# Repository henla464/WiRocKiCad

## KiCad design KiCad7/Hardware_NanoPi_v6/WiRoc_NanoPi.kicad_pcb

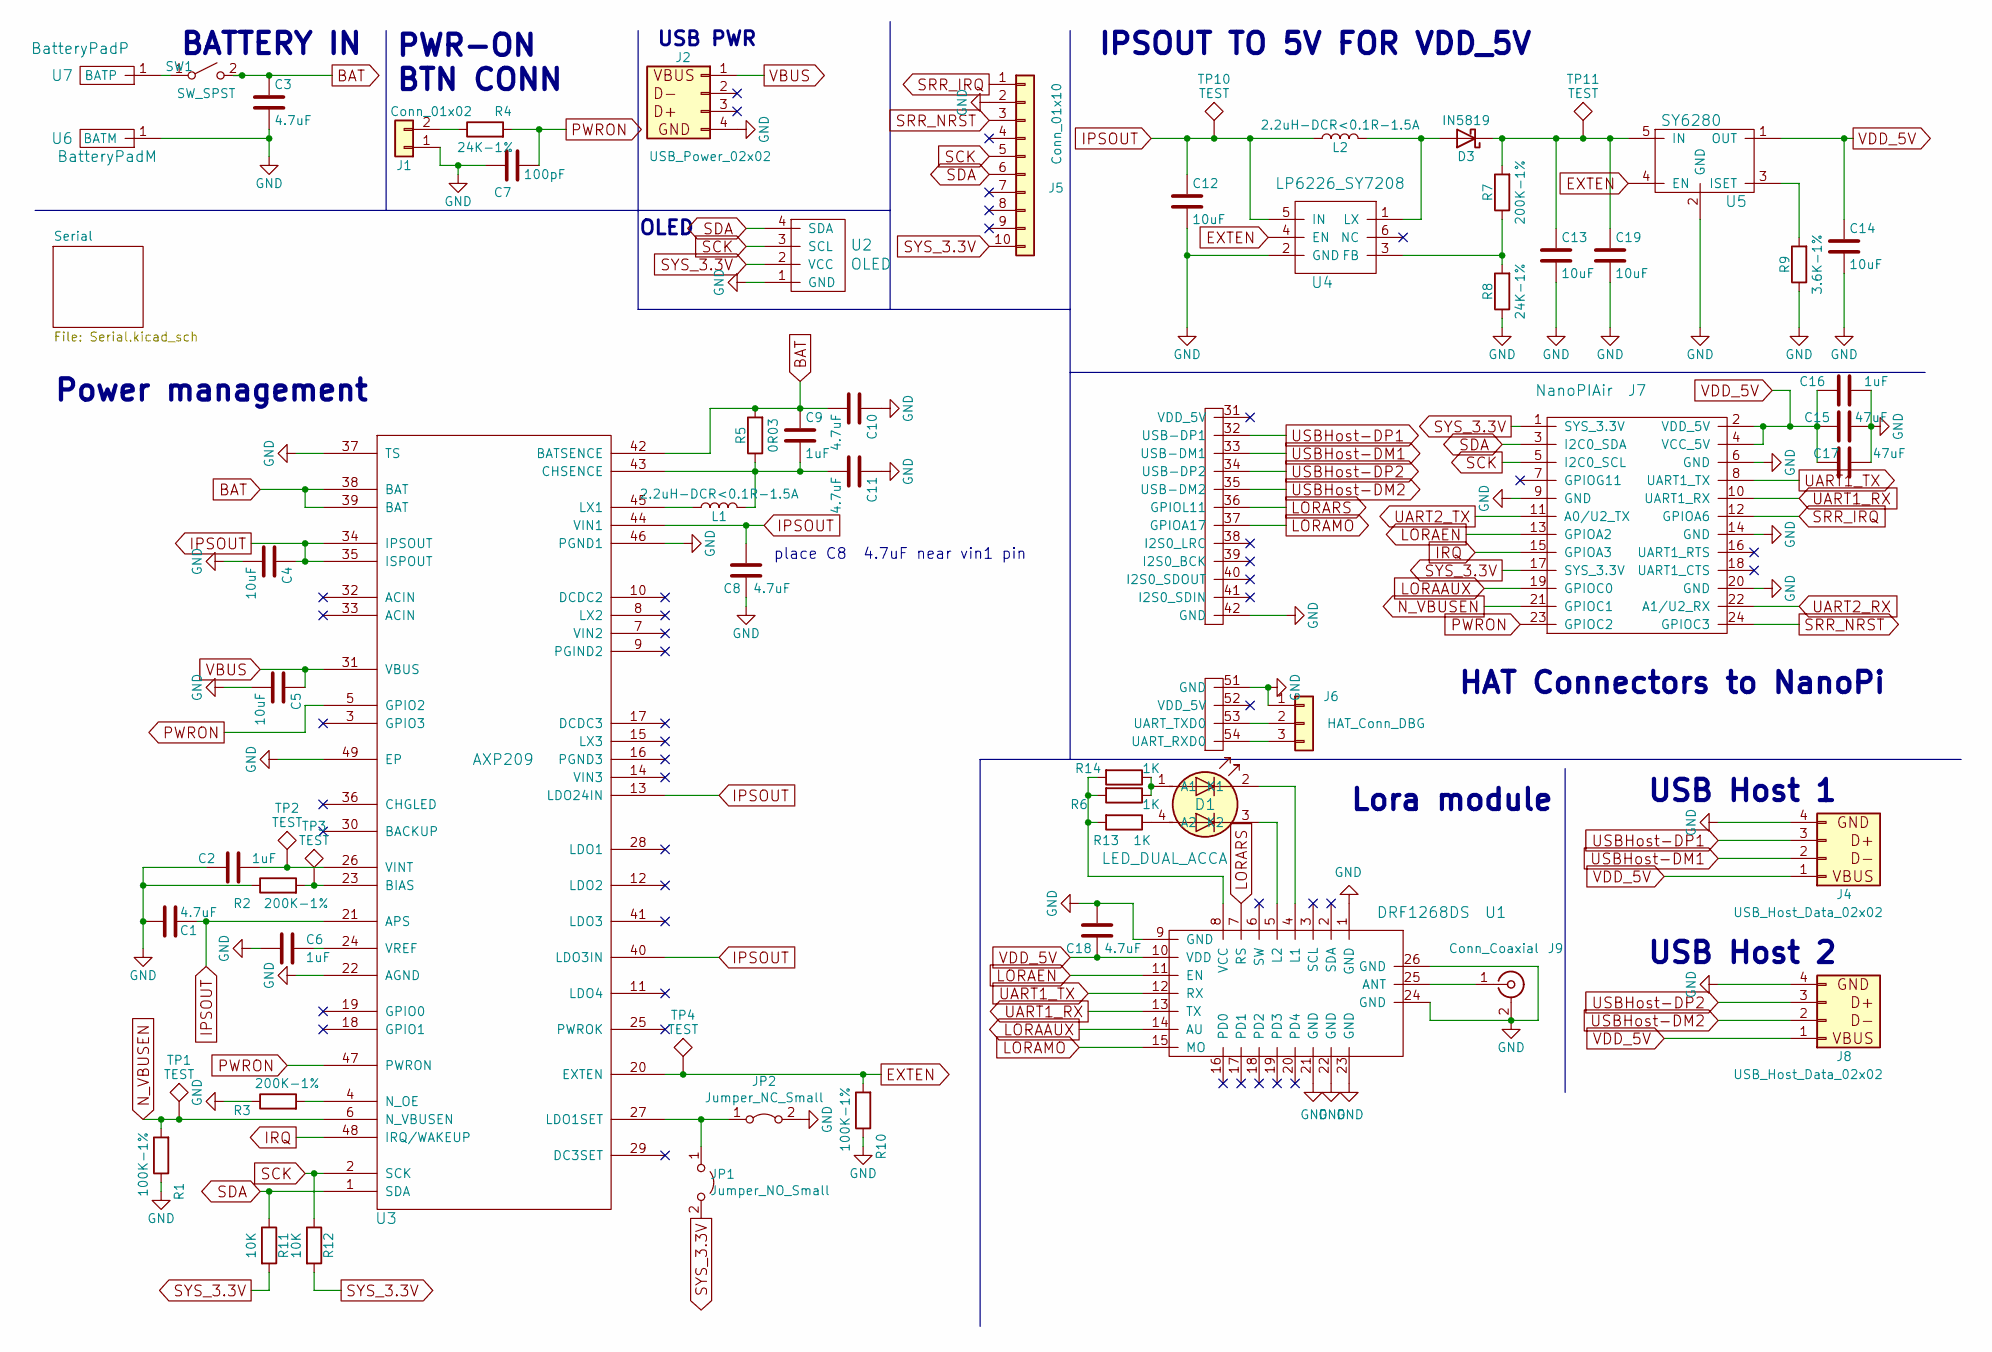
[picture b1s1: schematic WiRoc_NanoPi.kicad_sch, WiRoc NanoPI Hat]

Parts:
C1, C3, C8, C10, C11, C18: 4.7uF; C_0603_1608Metric; ManufacturerPartNumber CL10A475KO8NNNC; LCSC Part # C19666
C2, C6, C9, C16: 1uF; C_0603_1608Metric; ManufacturerPartNumber CL10A105KB8NNNC; LCSC Part # C15849
C4, C5, C12, C13, C14, C19: 10uF; C_0603_1608Metric; ManufacturerPartNumber CL10A106KP8NNNC; LCSC Part # C19702
C7: 100pF; C_0603_1608Metric; ManufacturerPartNumber CL10C101JB8NNNC; LCSC Part # C14858
C15: 47uF; C_1206_3216Metric; ManufacturerPartNumber CL31A476MPHNNNE; LCSC Part # C96123
C17: 47uF; C_1206_3216Metric; ManufacturerPartNumber CL31A476MPHNNNE; LCSC Part # C93123
D1: LED_DUAL_ACCA; LED_Dual_1.7_1.6; ManufacturerPartNumber HL-PCB-1617S9FH203BC; LCSC Part # C513363
D3: IN5819; D_SOD-123; ManufacturerPartNumber B5819W SL; LCSC Part # C8598
J1: Conn_01x02; Pin_Header_Straight_1x02_Pitch2.54mm; ManufacturerPartNumber 2.54mm 1x40P
J2: USB_Power_02x02; USBConnPads5
J4: USB_Host_Data_02x02; USBConnPads5
J5: Conn_01x10; FPC-Connector_1x10-1MP_P0.5mm_Horizontal; ManufacturerPartNumber X05B20U10T; LCSC Part # C388696
J6: HAT_Conn_DBG; Pin_Header_Straight_1x03_Pitch2.54mm; ManufacturerPartNumber 2.54mm 1x40P
J7: NanoPIAir; NanoPiNeoAirAllPins; ManufacturerPartNumber 2.54mm 2x40P
J8: USB_Host_Data_02x02; USBConnPads6
J9: Conn_Coaxial; SMA_Amphenol_901-143_Horizontal
JP1: Jumper_NO_Small; SolderJumper-2_P1.3mm_Open_Pad1.0x1.5mm-Modified
JP2: Jumper_NC_Small; SolderJumper-2_P1.3mm_Bridged2Bar_Pad1.0x1.5mm-Modified
L1, L2: 2.2uH-DCR<0.1R-1.5A; Inductor_SLW4018; ManufacturerPartNumber SLW4018S2R2MST; LCSC Part # C206341
R1, R10: 100K-1%; R_0603_1608Metric; ManufacturerPartNumber 0603WAF1003T5E; LCSC Part # C25803
R2, R3, R7: 200K-1%; R_0603_1608Metric; ManufacturerPartNumber 0603WAF2003T5E; LCSC Part # C25811
R4, R8: 24K-1%; R_0603_1608Metric; ManufacturerPartNumber 0603WAF2402T5E; LCSC Part # C23352
R5: 0R03; R_0805_2012Metric; ManufacturerPartNumber 0805W4F300MT5E; LCSC Part # C247605
R6, R13, R14: 1K; R_0603_1608Metric; ManufacturerPartNumber 0603WAJ0102T5E; LCSC Part # C25585
R9: 3.6K-1%; R_0603_1608Metric; ManufacturerPartNumber 0603WAF3601T5E; LCSC Part # C22980
R11, R12: 10K; R_0603_1608Metric; ManufacturerPartNumber 0603WAF1002T5E; LCSC Part # C25804
SW1: SW_SPST; Pin_Header_Straight_1x02_Pitch2.54mm; ManufacturerPartNumber 2.54mm 1x40P
TP1, TP2, TP3, TP4, TP10, TP11: TEST; TestPoint_Pad_D1.0mm
U1: DRF1268DS
U2: OLED; CONN_OLED_TWI-Socket_Strip_Straight_1x04_Pitch2.54mm; ManufacturerPartNumber 2.54mm 1x40P
U3: AXP209; qfn48_6x6mm_Pitch0.4mm; ManufacturerPartNumber AXP209; LCSC Part # C2997895
U4: LP6226_SY7208; SOT-23-6; ManufacturerPartNumber SY7208ABC; LCSC Part # C80514
U5: SY6280; SOT-23-5; ManufacturerPartNumber SY6280AAC; LCSC Part # C55136
U6: BatteryPadM; BatteryPad
U7: BatteryPadP; BatteryPad

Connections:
BAT: C3.1, C9.1, C10.2, R5.2, SW1.2 (B), U3.38 (BAT), U3.39 (BAT), U3.42 (BATSENCE)
EXTEN: R10.2, TP4.1, U3.20 (EXTEN), U4.4 (EN), U5.4 (EN)
GND: C1.2, C2.2, C3.2, C4.2, C5.2, C6.2, C7.1, C8.1, C10.1, C11.1, C12.2, C13.2, C14.2, C15.1, C16.2, C17.1, C18.2, C19.2, J1.1, J2.4, J4.4, J5.2, J6.1, J7.6 (GND), J7.9 (GND), J7.14 (GND), J7.20 (GND), J7.42 (GND), J7.51 (GND), J8.4, J9.2 (Ext), JP2.2 (B), R1.1, R2.1, R3.1, R8.1, R9.1, R10.1, U1.1 (GND), U1.9 (GND), U1.21 (GND), U1.22 (GND), U1.23 (GND), U1.24 (GND), U1.26 (GND), U2.1 (GND), U3.22 (AGND), U3.37 (TS), U3.46 (PGND1), U3.49 (EP), U4.2 (GND), U5.2 (GND), U6.1 (BATM); also elsewhere on the board
IPSOUT: C1.1, C4.1, C8.2, C12.1, L2.1, TP10.1, U3.13 (LDO24IN), U3.21 (APS), U3.34 (IPSOUT), U3.35 (ISPOUT), U3.40 (LDO3IN), U3.44 (VIN1), U4.5 (IN)
IRQ: J7.15 (GPIOA3), U3.48 (IRQ/WAKEUP)
LORAAUX: J7.19 (GPIOC0), U1.14 (AU)
LORAEN: J7.13 (GPIOA2), U1.11 (EN)
LORAMO: J7.37 (GPIOA17), U1.15 (MO)
LORARS: J7.36 (GPIOL11), U1.7 (RS)
N_VBUSEN: J7.21 (GPIOC1), R1.2, TP1.1, U3.6 (N_VBUSEN)
unnamed: D1.1 (A1), R6.1, R14.1
unnamed: D1.4 (A2), R13.1
unnamed: D1.2 (K1), U1.4 (L1)
unnamed: D1.3 (K2), U1.5 (L2)
unnamed: D3.2 (A), L2.2, U4.1 (LX)
unnamed: C13.1, C19.1, D3.1 (K), R7.2, TP11.1, U5.5 (IN)
unnamed: J1.2, R4.1
unnamed: J6.2, J7.53 (UART_TXD0)
unnamed: J6.3, J7.54 (UART_RXD0)
unnamed: J9.1 (In), U1.25 (ANT)
unnamed: JP1.1 (A), JP2.1 (A), U3.27 (LDO1SET)
unnamed: SW1.1 (A), U7.1 (BATP)
unnamed: R6.2, R13.2, R14.2, U1.8 (VCC)
unnamed: R2.2, TP3.1, U3.23 (BIAS)
unnamed: C9.2, C11.2, L1.2, R5.1, U3.43 (CHSENCE)
unnamed: L1.1, U3.45 (LX1)
unnamed: R3.2, U3.4 (N_OE)
unnamed: C2.1, TP2.1, U3.26 (VINT)
unnamed: C6.1, U3.24 (VREF)
unnamed: R7.1, R8.2, U4.3 (FB)
unnamed: R9.2, U5.3 (ISET)
PWRON: C7.2, J7.23 (GPIOC2), R4.2, U3.5 (GPIO2), U3.47 (PWRON)
SCK: J5.5, J7.5 (I2C0_SCL), R12.1, U2.3 (SCL), U3.2 (SCK)
SDA: J5.6, J7.3 (I2C0_SDA), R11.1, U2.4 (SDA), U3.1 (SDA)
SRR_IRQ: J5.1, J7.12 (GPIOA6)
SRR_NRST: J5.3, J7.24 (GPIOC3)
SYS_3.3V: J5.10, J7.1 (SYS_3.3V), J7.17 (SYS_3.3V), JP1.2 (B), R11.2, R12.2, U2.2 (VCC); also elsewhere on the board
UART1_RX: J7.10 (UART1_RX), U1.13 (TX)
UART1_TX: J7.8 (UART1_TX), U1.12 (RX)
UART2_RX: J7.22 (A1/U2_RX); also elsewhere on the board
UART2_TX: J7.11 (A0/U2_TX); also elsewhere on the board
USBHost-DM1: J4.2, J7.33 (USB-DM1)
USBHost-DM2: J7.35 (USB-DM2), J8.2
USBHost-DP1: J4.3, J7.32 (USB-DP1)
USBHost-DP2: J7.34 (USB-DP2), J8.3
VBUS: C5.1, J2.1, U3.31 (VBUS)
VDD_5V: C14.1, C15.2, C16.1, C17.2, C18.1, J4.1, J7.2 (VDD_5V), J7.4 (VCC_5V), J8.1, U1.10 (VDD), U5.1 (OUT)

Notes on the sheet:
place C8 4.7uF near vin1 pin
USB PWR
USB Host 2
Lora module
HAT Connectors to NanoPi
IPSOUT TO 5V FOR VDD_5V
PWR-ON BTN CONN
Power management
OLED
USB Host 1
BATTERY IN

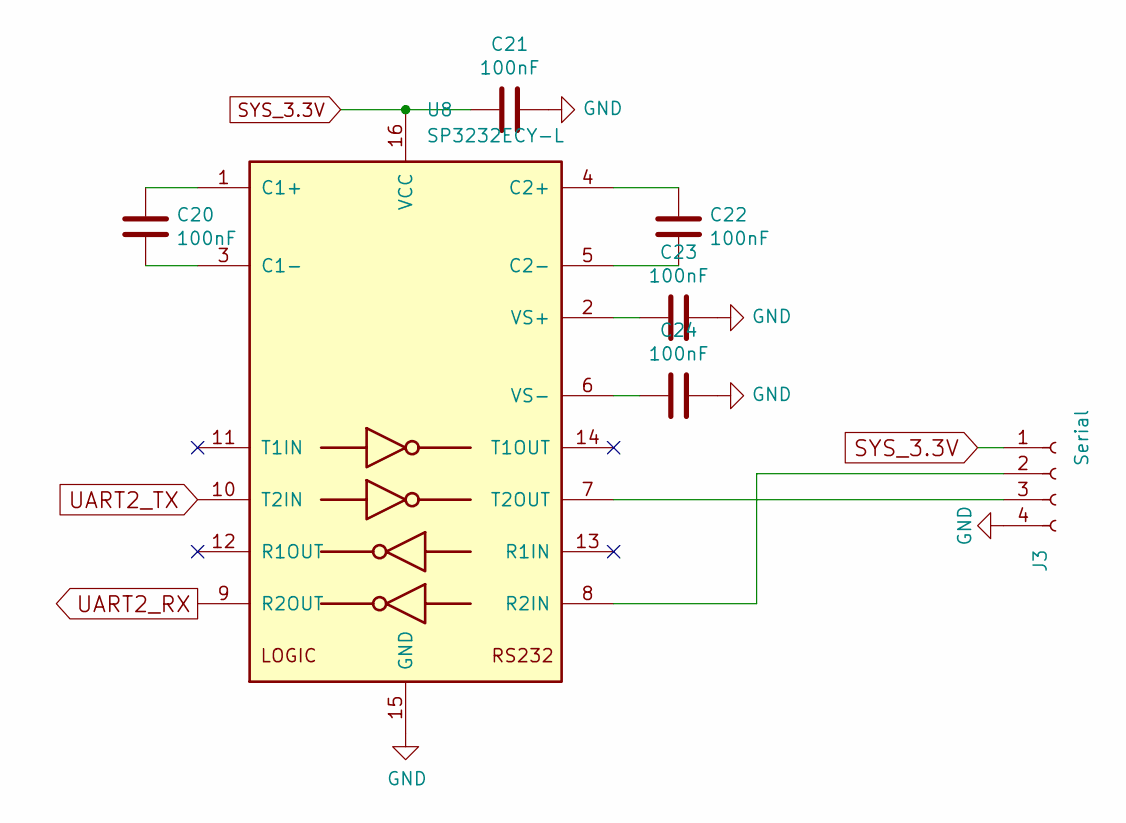
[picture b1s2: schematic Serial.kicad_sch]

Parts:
C20, C21, C22, C23, C24: 100nF; C_0603_1608Metric; ManufacturerPartNumber CC0603KRX7R9BB104; LCSC Part # C14663
J3: Serial; SerialConnPads
U8: SP3232ECY-L; TSSOP-16_4.4x5mm_P0.65mm; ManufacturerPartNumber SP3232ECY-L; LCSC Part # C31142

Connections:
GND: C21.1, C23.1, C24.1, J3.4, U8.15 (GND); also elsewhere on the board
unnamed: J3.2, U8.8 (R2IN)
unnamed: J3.3, U8.7 (T2OUT)
unnamed: C20.1, U8.1 (C1+)
unnamed: C20.2, U8.3 (C1-)
unnamed: C22.1, U8.4 (C2+)
unnamed: C22.2, U8.5 (C2-)
unnamed: C23.2, U8.2 (VS+)
unnamed: C24.2, U8.6 (VS-)
SYS_3.3V: C21.2, J3.1, U8.16 (VCC); also elsewhere on the board
UART2_RX: U8.9 (R2OUT); also elsewhere on the board
UART2_TX: U8.10 (T2IN); also elsewhere on the board

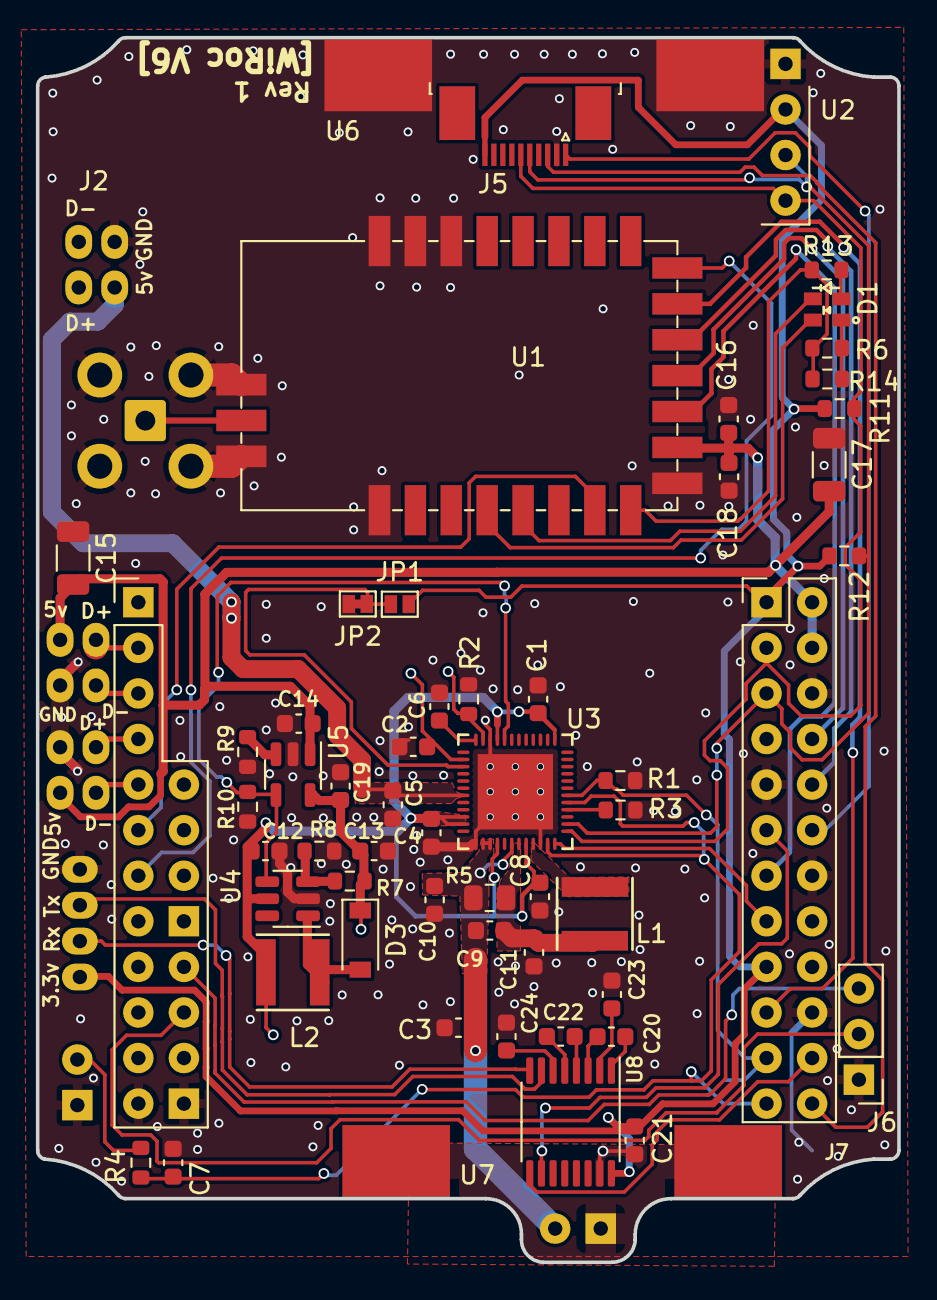
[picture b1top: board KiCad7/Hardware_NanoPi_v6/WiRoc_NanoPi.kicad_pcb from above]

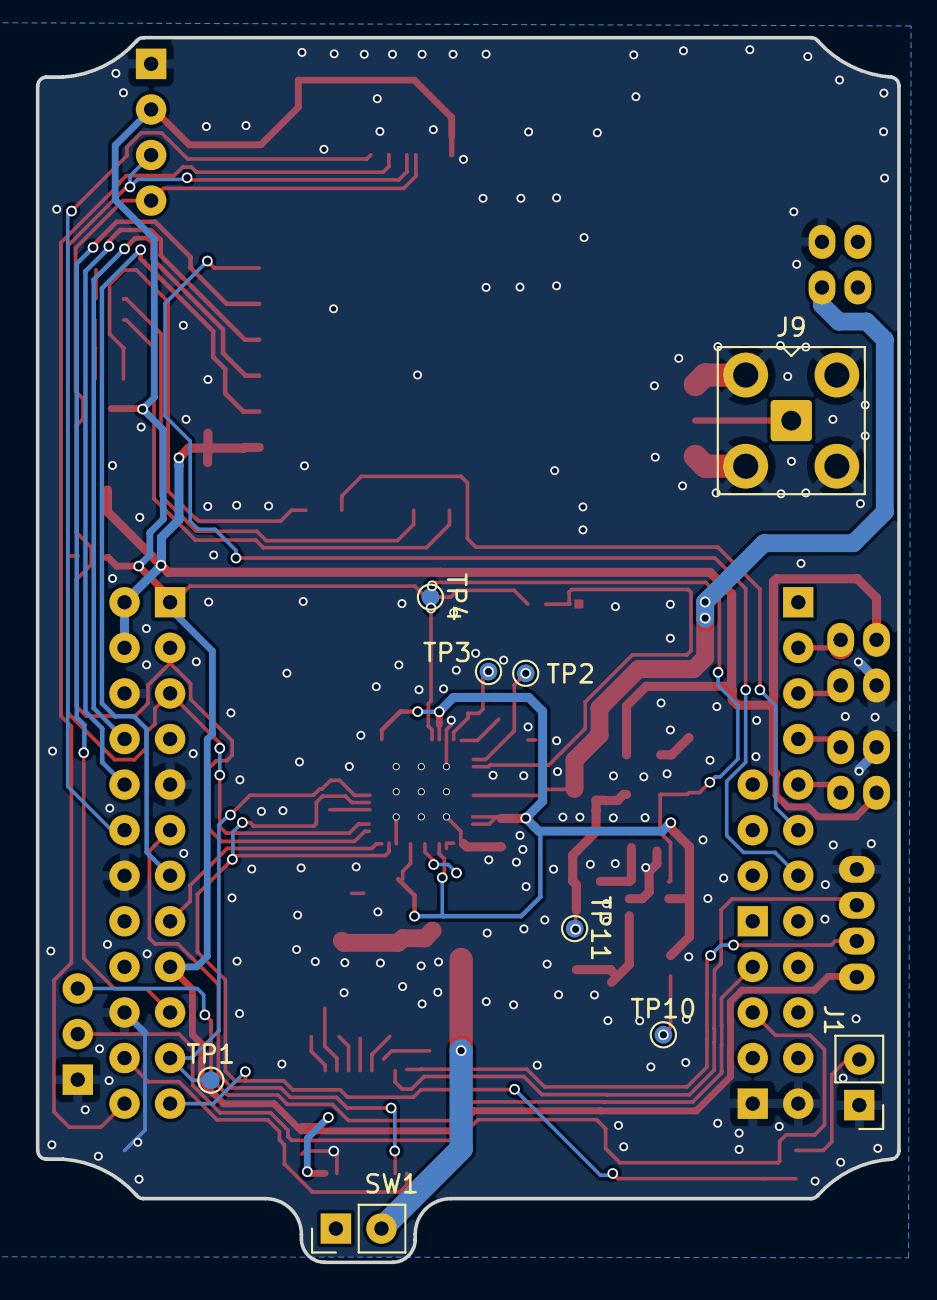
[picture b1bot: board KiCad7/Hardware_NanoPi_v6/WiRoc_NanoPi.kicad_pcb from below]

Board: 4 copper layers, 48.0 x 68.2 mm, 68 parts (9 on the bottom side), 55 nets.

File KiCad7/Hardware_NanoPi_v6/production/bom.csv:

Designator,Footprint,Quantity,Value,LCSC Part #
"C1, C10, C11, C18, C3, C8",0603,6,4.7uF,C19666
"C12, C13, C14, C19, C4, C5",0603,6,10uF,C19702
"C15, C17",1206,2,47uF,C93123
"C16, C2, C6, C9",0603,4,1uF,C15849
"C20, C21, C22, C23, C24",0603,5,100nF,C14663
C7,0603,1,100pF,C14858
D1,LED_Dual_1.7_1.6,1,LED_DUAL_ACCA,C513363
D3,D_SOD-123,1,IN5819,C8598
J5,FPC-Connector_1x10-1MP_P0.5mm_Horizontal,1,Conn_01x10,C388696
"L1, L2",Inductor_SLW4018,2,2.2uH-DCR<0.1R-1.5A,C206341
"R1, R10",0603,2,100K-1%,C25803
"R11, R12",0603,2,10K,C25804
"R13, R14, R6",0603,3,1K,C25585
"R2, R3, R7",0603,3,200K-1%,C25811
"R4, R8",0603,2,24K-1%,C23352
R5,0805,1,0R03,C247605
R9,0603,1,3.6K-1%,C22980
U3,qfn48_6x6mm_Pitch0.4mm,1,AXP209,C2997895
U4,SOT-23-6,1,LP6226_SY7208,C80514
U5,SOT-23-5,1,SY6280,C55136
U8,TSSOP-16_4.4x5mm_P0.65mm,1,SP3232ECY-L,C31142

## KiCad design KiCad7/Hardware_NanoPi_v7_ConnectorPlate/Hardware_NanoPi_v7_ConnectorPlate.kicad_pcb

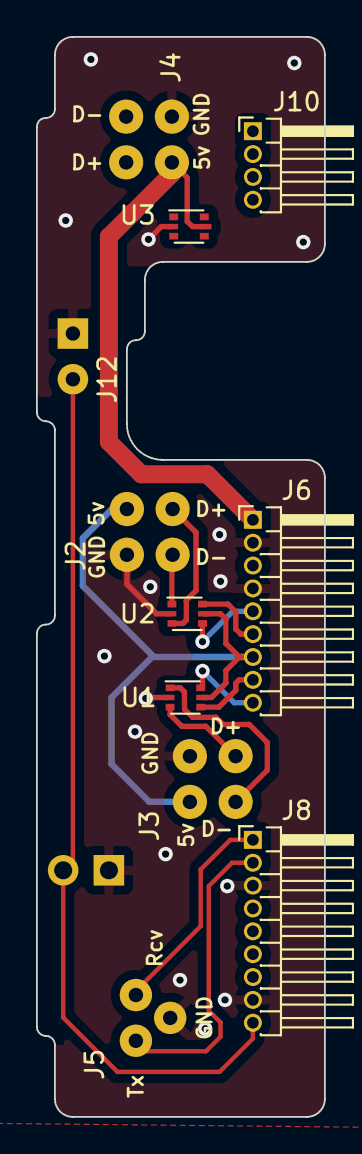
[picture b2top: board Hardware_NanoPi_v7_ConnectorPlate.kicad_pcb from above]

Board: 2 copper layers, 16.0 x 60.0 mm, 12 parts (1 on the bottom side), 14 nets.

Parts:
J2: USB_Host_Data_02x02; USBConnPads7
J3: USB_Host_Data_02x02; USBConnPads8
J4: USB_Power_02x02; USBConnPads7
J5: Conn_01x03; SerialConnPads3Pin
J6, J8: Conn_01x09; PinHeader_1x09_P1.27mm_Horizontal
J10: Conn_01x04; PinHeader_1x04_P1.27mm_Horizontal
J11: Conn_01x02; PinHeader_1x02_P2.54mm_Horizontal
J12: Conn_01x02; PwrBtnPads
U1, U2, U3: USBLC6-2P6; SOT-666

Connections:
GND: J2.4, J3.4, J4.4, J5.3, J6.2, J6.4, J8.3, J8.8, J11.1, J12.1, U1.2 (GND), U2.2 (GND), U3.2 (GND)
unnamed: J2.2, U2.1 (I/O1)
unnamed: J2.3, U2.3 (I/O2)
unnamed: J3.2, U1.1 (I/O1)
unnamed: J3.3, U1.3 (I/O2)
PWRBTN: J8.9, J11.2, J12.2
R2IN: J5.1, J8.2
T2OUT: J5.2, J8.1
USBHost-DM1: J6.6, U2.6 (I/O1)
USBHost-DM2: J6.9, U1.6 (I/O1)
USBHost-DP1: J6.5, U2.4 (I/O2)
USBHost-DP2: J6.8, U1.4 (I/O2)
VBUS: J4.1, J6.1, U3.5 (VBUS)
VDD_5V: J2.1, J3.1, J6.7, U1.5 (VBUS), U2.5 (VBUS)

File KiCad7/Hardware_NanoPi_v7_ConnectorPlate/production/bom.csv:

Designator,Footprint,Quantity,Value,LCSC Part #
J10,PinHeader_1x04_P1.27mm_Horizontal,1,Conn_01x04,
J11,PinHeader_1x02_P2.54mm_Horizontal,1,Conn_01x02,
J12,PwrBtnPads,1,Conn_01x02,
J5,SerialConnPads3Pin,1,Conn_01x03,
"J6, J8",PinHeader_1x09_P1.27mm_Horizontal,2,Conn_01x09,
"U1, U2, U3",SOT-666,3,USBLC6-2P6,

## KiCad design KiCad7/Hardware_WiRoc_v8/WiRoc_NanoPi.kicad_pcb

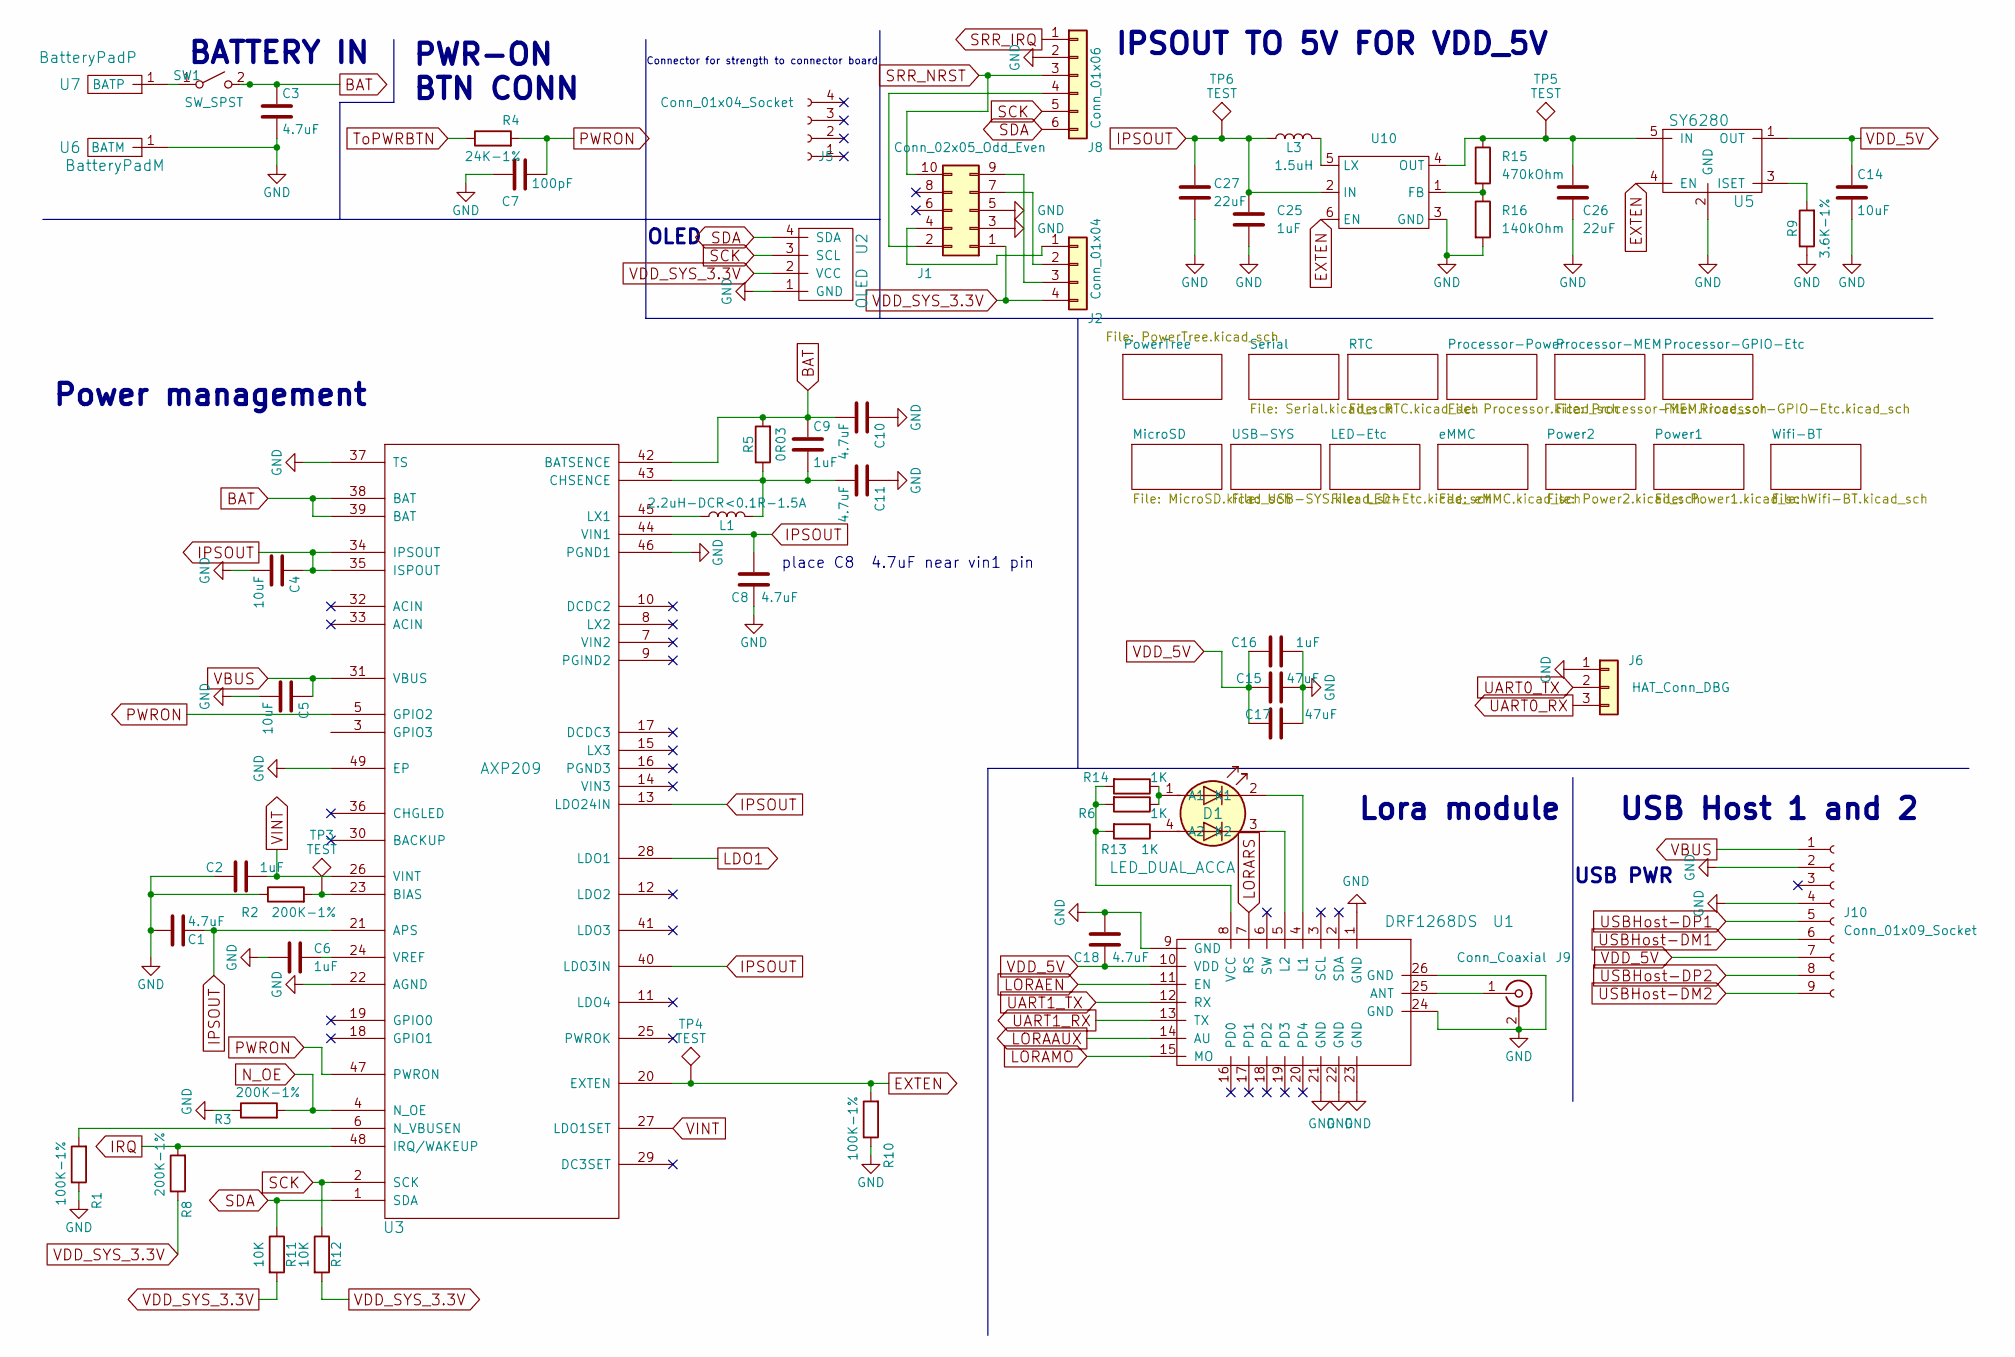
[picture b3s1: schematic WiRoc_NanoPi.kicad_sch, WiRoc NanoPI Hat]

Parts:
C1, C3, C8, C10, C11, C18: 4.7uF; C_0402_1005Metric; ManufacturerPartNumber CL10A475KO8NNNC; LCSC Part # C19666
C2, C6, C9, C16, C25: 1uF; C_0402_1005Metric; ManufacturerPartNumber CL10A105KB8NNNC; LCSC Part # C15849
C4, C5, C14: 10uF; C_0402_1005Metric; ManufacturerPartNumber CL10A106KP8NNNC; LCSC Part # C19702
C7: 100pF; C_0402_1005Metric; ManufacturerPartNumber CL10C101JB8NNNC; LCSC Part # C14858
C15, C17: 47uF; C_1206_3216Metric; ManufacturerPartNumber CL31A476MPHNNNE; LCSC Part # C96123
C26, C27: 22uF; C_0402_1005Metric; PartNo GRM188R61A226ME15D; LCSC Part # C84419
D1: LED_DUAL_ACCA; LED_Dual_1.7_1.6; ManufacturerPartNumber HL-PCB-1617S9FH203BC; LCSC Part # C513363
J1: Conn_02x05_Odd_Even; PinHeader_2x05_P1.27mm_Vertical
J2: Conn_01x04; PinHeader_1x04_P1.27mm_Horizontal
J5: Conn_01x04_Socket; PinSocket_1x04_P1.27mm_Vertical
J6: HAT_Conn_DBG; Pin_Header_Straight_1x03_Pitch2.54mm; ManufacturerPartNumber 2.54mm 1x40P
J8: Conn_01x06; PinHeader_1x06_P1.27mm_Horizontal
J9: Conn_Coaxial; SMA_Amphenol_901-143_Horizontal
J10: Conn_01x09_Socket; PinSocket_1x09_P1.27mm_Vertical
L1: 2.2uH-DCR<0.1R-1.5A; Inductor_SLW4018; ManufacturerPartNumber SLW4018S2R2MST; LCSC Part # C206341
L3: 1.5uH; Inductor_SLW4018; PartNo SLW4020S1R5MST; LCSC Part # C206395
R1, R10: 100K-1%; R_0402_1005Metric; ManufacturerPartNumber 0603WAF1003T5E; LCSC Part # C25803
R2, R3, R8: 200K-1%; R_0402_1005Metric; ManufacturerPartNumber 0603WAF2003T5E; LCSC Part # C25811
R4: 24K-1%; R_0402_1005Metric; ManufacturerPartNumber 0603WAF2402T5E; LCSC Part # C23352
R5: 0R03; R_0805_2012Metric; ManufacturerPartNumber 0805W4F300MT5E; LCSC Part # C247605
R6, R13, R14: 1K; R_0402_1005Metric; ManufacturerPartNumber 0603WAJ0102T5E; LCSC Part # C21190
R9: 3.6K-1%; R_0402_1005Metric; ManufacturerPartNumber 0603WAF3601T5E; LCSC Part # C22980
R11, R12: 10K; R_0402_1005Metric; ManufacturerPartNumber 0603WAF1002T5E; LCSC Part # C25804
R15: 470kOhm; R_0402_1005Metric; PartNo HPCR0603F470KK9; LCSC Part # C23178
R16: 140kOhm; R_0402_1005Metric; PartNo 0603WAF140KT5E; LCSC Part # C321721
SW1: SW_SPST; Pin_Header_Straight_1x02_Pitch2.54mm; ManufacturerPartNumber 2.54mm 1x40P
TP3, TP4, TP5, TP6: TEST; TestPoint_Pad_D1.0mm
U1: DRF1268DS
U2: OLED; CONN_OLED_TWI-Socket_Strip_Straight_1x04_Pitch2.54mm; ManufacturerPartNumber 2.54mm 1x40P
U3: AXP209; qfn48_6x6mm_Pitch0.4mm; ManufacturerPartNumber AXP209; LCSC Part # C2997895
U5: SY6280; SOT-23-5; ManufacturerPartNumber SY6280AAC; LCSC Part # C55136
U6: BatteryPadM; BatteryPad
U7: BatteryPadP; BatteryPadThinner
U10: TSOT-23-6; PartNo SY7069ADC; LCSC Part # C207630

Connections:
BAT: C3.1, C9.1, C10.2, R5.2, SW1.2 (B), U3.38 (BAT), U3.39 (BAT), U3.42 (BATSENCE)
EXTEN: R10.2, TP4.1, U3.20 (EXTEN), U5.4 (EN), U10.6 (EN)
GND: C1.2, C2.2, C3.2, C4.2, C5.2, C6.2, C7.1, C8.1, C10.1, C11.1, C14.2, C15.1, C16.2, C17.1, C18.2, C25.2, C26.2, C27.2, J1.3, J1.5, J6.1, J8.2, J9.2 (Ext), J10.2, J10.4, R1.1, R2.1, R3.1, R9.1, R10.1, R16.2, U1.1 (GND), U1.9 (GND), U1.21 (GND), U1.22 (GND), U1.23 (GND), U1.24 (GND), U1.26 (GND), U2.1 (GND), U3.22 (AGND), U3.37 (TS), U3.46 (PGND1), U3.49 (EP), U5.2 (GND), U6.1 (BATM), U10.3 (GND); also elsewhere on the board
IPSOUT: C1.1, C4.1, C8.2, C25.1, C27.1, L3.1, TP6.1, U3.13 (LDO24IN), U3.21 (APS), U3.34 (IPSOUT), U3.35 (ISPOUT), U3.40 (LDO3IN), U3.44 (VIN1), U10.2 (IN)
IRQ: R8.2, U3.48 (IRQ/WAKEUP); also elsewhere on the board
LDO1: U3.28 (LDO1); also elsewhere on the board
LORAAUX: U1.14 (AU); also elsewhere on the board
LORAEN: U1.11 (EN); also elsewhere on the board
LORAMO: U1.15 (MO); also elsewhere on the board
LORARS: U1.7 (RS); also elsewhere on the board
N_OE: R3.2, U3.4 (N_OE); also elsewhere on the board
unnamed: D1.1 (A1), R6.1, R14.1
unnamed: D1.4 (A2), R13.1
unnamed: D1.2 (K1), U1.4 (L1)
unnamed: D1.3 (K2), U1.5 (L2)
unnamed: J1.2, J8.4
unnamed: J1.4, J2.1
unnamed: J1.7, J2.2
unnamed: J1.9, J2.3
unnamed: J9.1 (In), U1.25 (ANT)
unnamed: SW1.1 (A), U7.1 (BATP)
unnamed: R6.2, R13.2, R14.2, U1.8 (VCC)
unnamed: R2.2, TP3.1, U3.23 (BIAS)
unnamed: C9.2, C11.2, L1.2, R5.1, U3.43 (CHSENCE)
unnamed: L1.1, U3.45 (LX1)
unnamed: R1.2, U3.6 (N_VBUSEN)
unnamed: C6.1, U3.24 (VREF)
unnamed: R9.2, U5.3 (ISET)
unnamed: R15.2, R16.1, U10.1 (FB)
unnamed: L3.2, U10.5 (LX)
unnamed: C26.1, R15.1, TP5.1, U5.5 (IN), U10.4 (OUT)
PWRON: C7.2, R4.2, U3.5 (GPIO2), U3.47 (PWRON)
SCK: J8.5, R12.1, U2.3 (SCL), U3.2 (SCK); also elsewhere on the board
SDA: J8.6, R11.1, U2.4 (SDA), U3.1 (SDA); also elsewhere on the board
SRR_IRQ: J8.1; also elsewhere on the board
SRR_NRST: J1.10, J8.3; also elsewhere on the board
ToPWRBTN: R4.1; also elsewhere on the board
UART0_RX: J6.3; also elsewhere on the board
UART0_TX: J6.2; also elsewhere on the board
UART1_RX: U1.13 (TX); also elsewhere on the board
UART1_TX: U1.12 (RX); also elsewhere on the board
USBHost-DM1: J10.6; also elsewhere on the board
USBHost-DM2: J10.9; also elsewhere on the board
USBHost-DP1: J10.5; also elsewhere on the board
USBHost-DP2: J10.8; also elsewhere on the board
VBUS: C5.1, J10.1, U3.31 (VBUS)
VDD_5V: C14.1, C15.2, C16.1, C17.2, C18.1, J10.7, U1.10 (VDD), U5.1 (OUT); also elsewhere on the board
VDD_SYS_3.3V: J1.1, J2.4, R8.1, R11.2, R12.2, U2.2 (VCC); also elsewhere on the board
VINT: C2.1, U3.26 (VINT), U3.27 (LDO1SET)

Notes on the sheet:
place C8 4.7uF near vin1 pin
USB PWR
Lora module
IPSOUT TO 5V FOR VDD_5V
PWR-ON BTN CONN
Power management
OLED
Connector for strength to connector board
USB Host 1 and 2
BATTERY IN

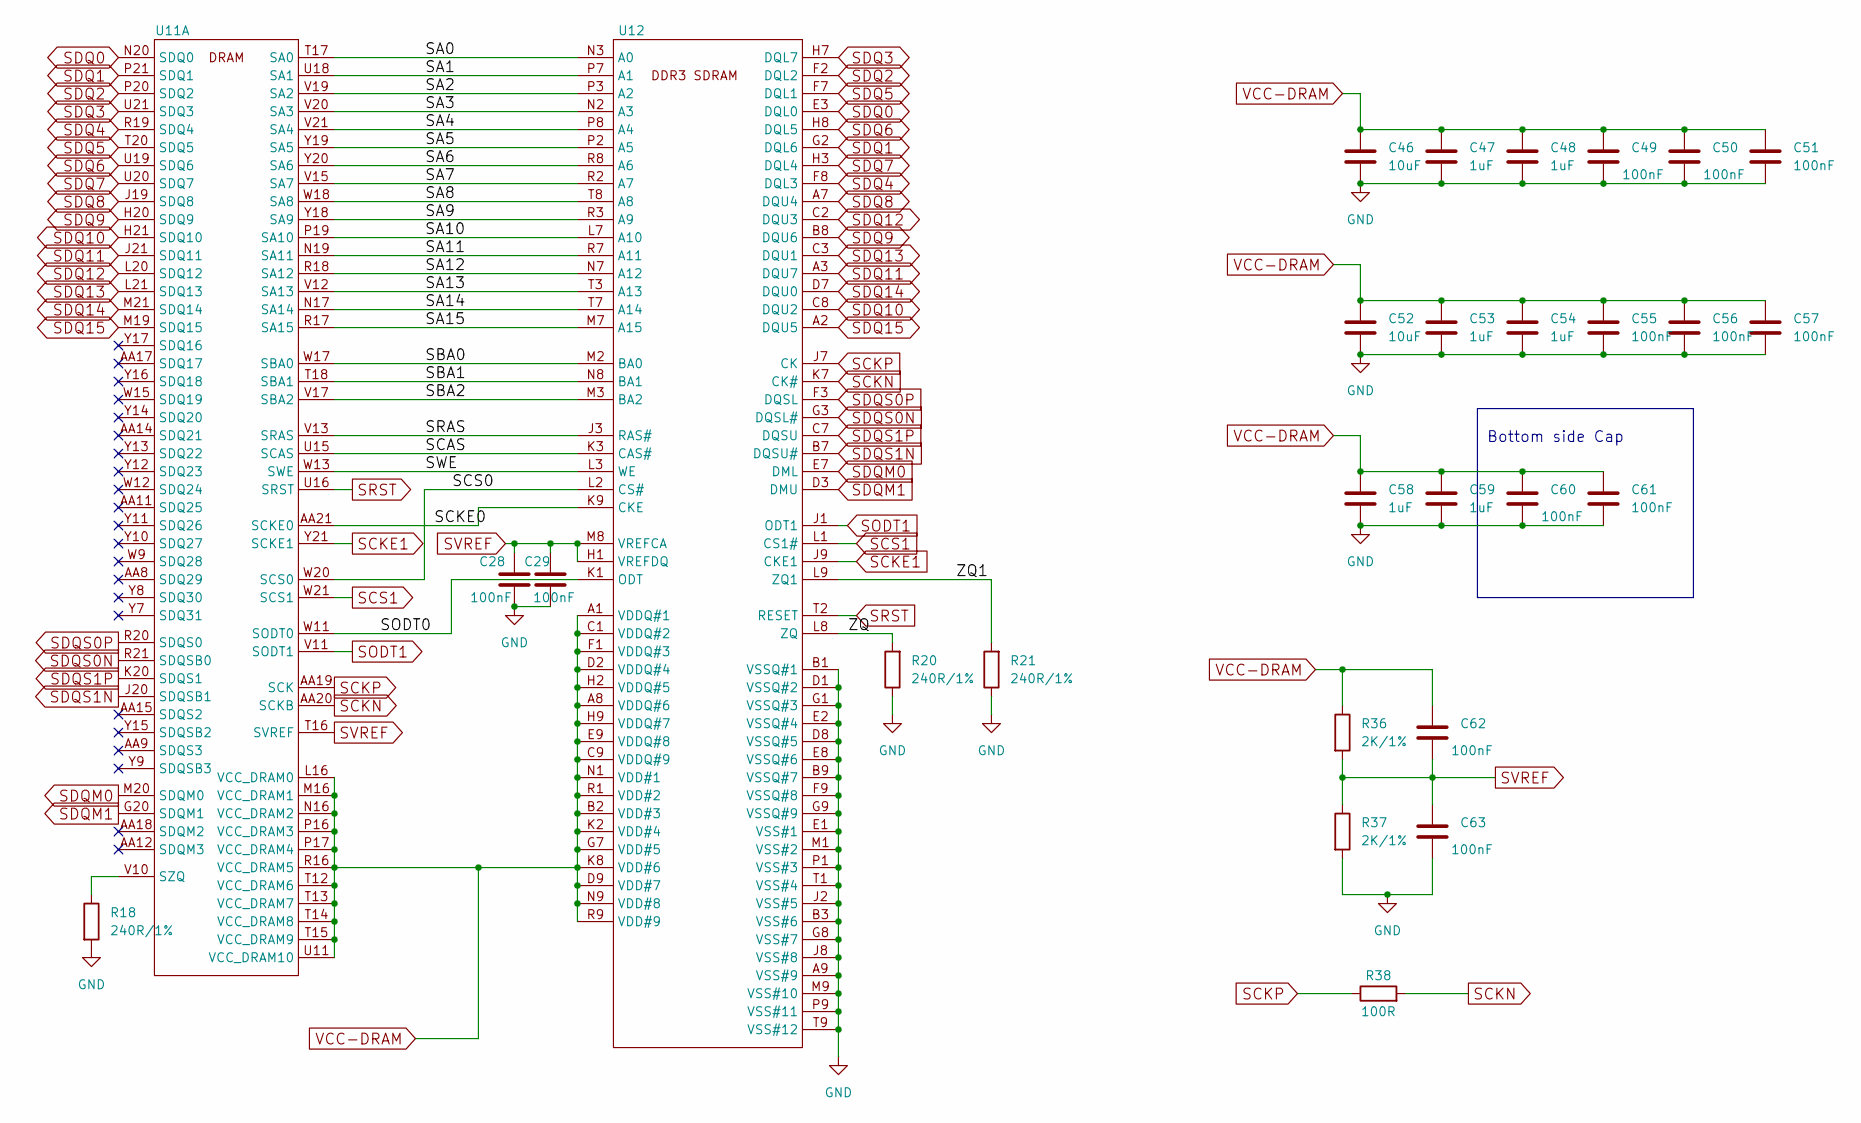
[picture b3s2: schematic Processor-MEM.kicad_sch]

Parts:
C28, C29, C49, C50, C51, C55, C56, C57, C60, C61, C62, C63: 100nF; C_0402_1005Metric
C46, C52: 10uF; C_0402_1005Metric
C47, C48, C53, C54, C58, C59: 1uF; C_0402_1005Metric
R18, R20, R21: 240R/1%; R_0402_1005Metric
R36, R37: 2K/1%; R_0402_1005Metric
R38: 100R; R_0402_1005Metric
U11: BGA-347_21x21_14.0x14.0mm
U12: BGA-96_9.0x13.0mm_Layout2x3x16_P0.8mm

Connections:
/Processor-MEM/SA0: U11.T17 (SA0), U12.N3 (A0)
/Processor-MEM/SA1: U11.U18 (SA1), U12.P7 (A1)
/Processor-MEM/SA2: U11.V19 (SA2), U12.P3 (A2)
/Processor-MEM/SA3: U11.V20 (SA3), U12.N2 (A3)
/Processor-MEM/SA4: U11.V21 (SA4), U12.P8 (A4)
/Processor-MEM/SA5: U11.Y19 (SA5), U12.P2 (A5)
/Processor-MEM/SA6: U11.Y20 (SA6), U12.R8 (A6)
/Processor-MEM/SA7: U11.V15 (SA7), U12.R2 (A7)
/Processor-MEM/SA8: U11.W18 (SA8), U12.T8 (A8)
/Processor-MEM/SA9: U11.Y18 (SA9), U12.R3 (A9)
/Processor-MEM/SA10: U11.P19 (SA10), U12.L7 (A10)
/Processor-MEM/SA11: U11.N19 (SA11), U12.R7 (A11)
/Processor-MEM/SA12: U11.R18 (SA12), U12.N7 (A12)
/Processor-MEM/SA13: U11.V12 (SA13), U12.T3 (A13)
/Processor-MEM/SA14: U11.N17 (SA14), U12.T7 (A14)
/Processor-MEM/SA15: U11.R17 (SA15), U12.M7 (A15)
/Processor-MEM/SBA0: U11.W17 (SBA0), U12.M2 (BA0)
/Processor-MEM/SBA1: U11.T18 (SBA1), U12.N8 (BA1)
/Processor-MEM/SBA2: U11.V17 (SBA2), U12.M3 (BA2)
/Processor-MEM/SCAS: U11.U15 (SCAS), U12.K3 (CAS#)
/Processor-MEM/SCKE0: U11.AA21 (SCKE0), U12.K9 (CKE)
/Processor-MEM/SCS0: U11.W20 (SCS0), U12.L2 (CS#)
/Processor-MEM/SODT0: U11.W11 (SODT0), U12.K1 (ODT)
/Processor-MEM/SRAS: U11.V13 (SRAS), U12.J3 (RAS#)
/Processor-MEM/SWE: U11.W13 (SWE), U12.L3 (WE)
/Processor-MEM/ZQ: R20.2, U12.L8 (ZQ)
/Processor-MEM/ZQ1: R21.2, U12.L9 (ZQ1)
GND: C28.2, C29.2, C46.2, C47.2, C48.2, C49.2, C50.2, C51.2, C52.2, C53.2, C54.2, C55.2, C56.2, C57.2, C58.2, C59.2, C60.2, C61.2, C63.2, R18.2, R20.1, R21.1, R37.2, U12.A9 (VSS#9), U12.B1 (VSSQ#1), U12.B3 (VSS#6), U12.B9 (VSSQ#7), U12.D1 (VSSQ#2), U12.D8 (VSSQ#5), U12.E1 (VSS#1), U12.E2 (VSSQ#4), U12.E8 (VSSQ#6), U12.F9 (VSSQ#8), U12.G1 (VSSQ#3), U12.G8 (VSS#7), U12.G9 (VSSQ#9), U12.J2 (VSS#5), U12.J8 (VSS#8), U12.M1 (VSS#2), U12.M9 (VSS#10), U12.P1 (VSS#3), U12.P9 (VSS#11), U12.T1 (VSS#4), U12.T9 (VSS#12); also elsewhere on the board
unnamed: R18.1, U11.V10 (SZQ)
SCKE1: U11.Y21 (SCKE1), U12.J9 (CKE1)
SCKN: R38.2, U11.AA20 (SCKB), U12.K7 (CK#)
SCKP: R38.1, U11.AA19 (SCK), U12.J7 (CK)
SCS1: U11.W21 (SCS1), U12.L1 (CS1#)
SDQ0: U11.N20 (SDQ0), U12.E3 (DQL0)
SDQ1: U11.P21 (SDQ1), U12.G2 (DQL6)
SDQ2: U11.P20 (SDQ2), U12.F2 (DQL2)
SDQ3: U11.U21 (SDQ3), U12.H7 (DQL7)
SDQ4: U11.R19 (SDQ4), U12.F8 (DQL3)
SDQ5: U11.T20 (SDQ5), U12.F7 (DQL1)
SDQ6: U11.U19 (SDQ6), U12.H8 (DQL5)
SDQ7: U11.U20 (SDQ7), U12.H3 (DQL4)
SDQ8: U11.J19 (SDQ8), U12.A7 (DQU4)
SDQ9: U11.H20 (SDQ9), U12.B8 (DQU6)
SDQ10: U11.H21 (SDQ10), U12.C8 (DQU2)
SDQ11: U11.J21 (SDQ11), U12.A3 (DQU7)
SDQ12: U11.L20 (SDQ12), U12.C2 (DQU3)
SDQ13: U11.L21 (SDQ13), U12.C3 (DQU1)
SDQ14: U11.M21 (SDQ14), U12.D7 (DQU0)
SDQ15: U11.M19 (SDQ15), U12.A2 (DQU5)
SDQM0: U11.M20 (SDQM0), U12.E7 (DML)
SDQM1: U11.G20 (SDQM1), U12.D3 (DMU)
SDQS0N: U11.R21 (SDQSB0), U12.G3 (DQSL#)
SDQS0P: U11.R20 (SDQS0), U12.F3 (DQSL)
SDQS1N: U11.J20 (SDQSB1), U12.B7 (DQSU#)
SDQS1P: U11.K20 (SDQS1), U12.C7 (DQSU)
SODT1: U11.V11 (SODT1), U12.J1 (ODT1)
SRST: U11.U16 (SRST), U12.T2 (RESET)
SVREF: C28.1, C29.1, C62.2, C63.1, R36.2, R37.1, U11.T16 (SVREF), U12.H1 (VREFDQ), U12.M8 (VREFCA)
VCC-DRAM: C46.1, C47.1, C48.1, C49.1, C50.1, C51.1, C52.1, C53.1, C54.1, C55.1, C56.1, C57.1, C58.1, C59.1, C60.1, C61.1, C62.1, R36.1, U11.L16 (VCC_DRAM0), U11.M16 (VCC_DRAM1), U11.N16 (VCC_DRAM2), U11.P16 (VCC_DRAM3), U11.P17 (VCC_DRAM4), U11.R16 (VCC_DRAM5), U11.T12 (VCC_DRAM6), U11.T13 (VCC_DRAM7), U11.T14 (VCC_DRAM8), U11.T15 (VCC_DRAM9), U11.U11 (VCC_DRAM10), U12.A1 (VDDQ#1), U12.A8 (VDDQ#6), U12.B2 (VDD#3), U12.C1 (VDDQ#2), U12.C9 (VDDQ#9), U12.D2 (VDDQ#4), U12.D9 (VDD#7), U12.E9 (VDDQ#8), U12.F1 (VDDQ#3), U12.G7 (VDD#5), U12.H2 (VDDQ#5), U12.H9 (VDDQ#7), U12.K2 (VDD#4), U12.K8 (VDD#6), U12.N1 (VDD#1), U12.N9 (VDD#8), U12.R1 (VDD#2), U12.R9 (VDD#9); also elsewhere on the board

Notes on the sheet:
Bottom side Cap

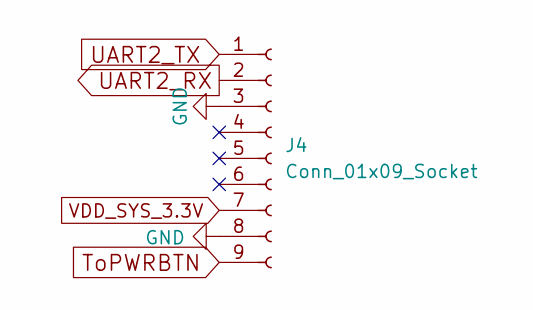
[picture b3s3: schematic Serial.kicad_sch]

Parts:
J4: Conn_01x09_Socket; PinSocket_1x09_P1.27mm_Vertical

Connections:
GND: J4.3, J4.8; also elsewhere on the board
ToPWRBTN: J4.9; also elsewhere on the board
UART2_RX: J4.2; also elsewhere on the board
UART2_TX: J4.1; also elsewhere on the board
VDD_SYS_3.3V: J4.7; also elsewhere on the board
